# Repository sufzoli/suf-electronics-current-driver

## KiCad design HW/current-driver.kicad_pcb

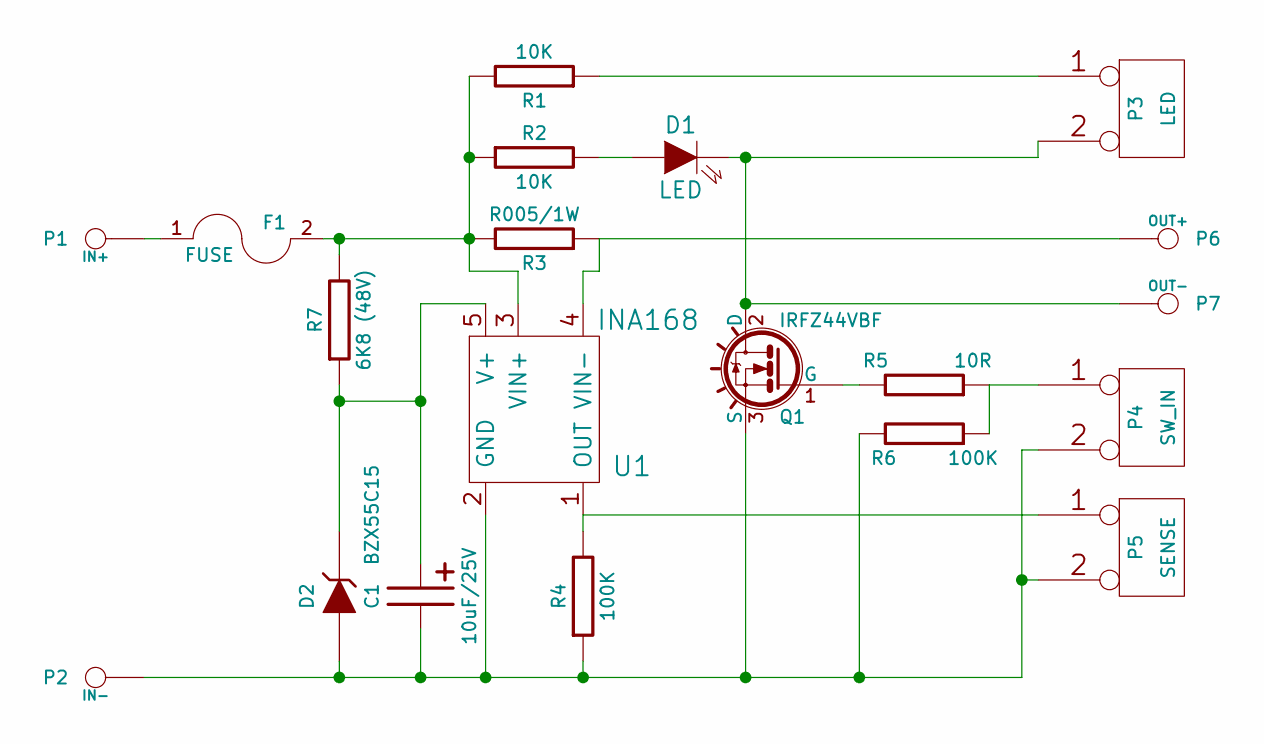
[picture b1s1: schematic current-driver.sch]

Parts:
C1: 10uF/25V; C1P_D2
D1: LED; LED3
D2: BZX55C15; D3
F1: FUSE; AUTOFUSE
P1: IN+; HEADER_6.3
P2: IN-; HEADER_6.3
P3: LED; HDR-2
P4: SW_IN; HDR-2
P5: SENSE; HDR-2
P6: OUT+; HEADER_6.3
P7: OUT-; HEADER_6.3
Q1: IRFZ44VBF; TO220
R1, R2: 10K; R4
R3: R005/1W; R4_5_6
R4, R6: 100K; R4
R5: 10R; R4
R7: 6K8 (48V); R4
U1: INA168; SOT23-5

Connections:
unnamed: Q1.1 (G), R5.1
unnamed: P4.1, R5.2, R6.2
unnamed: P5.1, R4.1, U1.1 (OUT)
unnamed: C1.1, D2.2 (K), R7.2, U1.5 (V+)
unnamed: P3.1, R1.2
unnamed: C1.2, D2.1 (A), P2.1, P4.2 (PM), P5.2 (PM), Q1.3 (S), R4.2, R6.1, U1.2 (GND)
unnamed: D1.2 (K), P3.2 (PM), P7.1, Q1.2 (D)
unnamed: P6.1, R3.2, U1.4 (VIN-)
unnamed: D1.1 (A), R2.1
unnamed: F1.1, P1.1
unnamed: F1.2, R1.1, R2.2, R3.1, R7.1, U1.3 (VIN+)

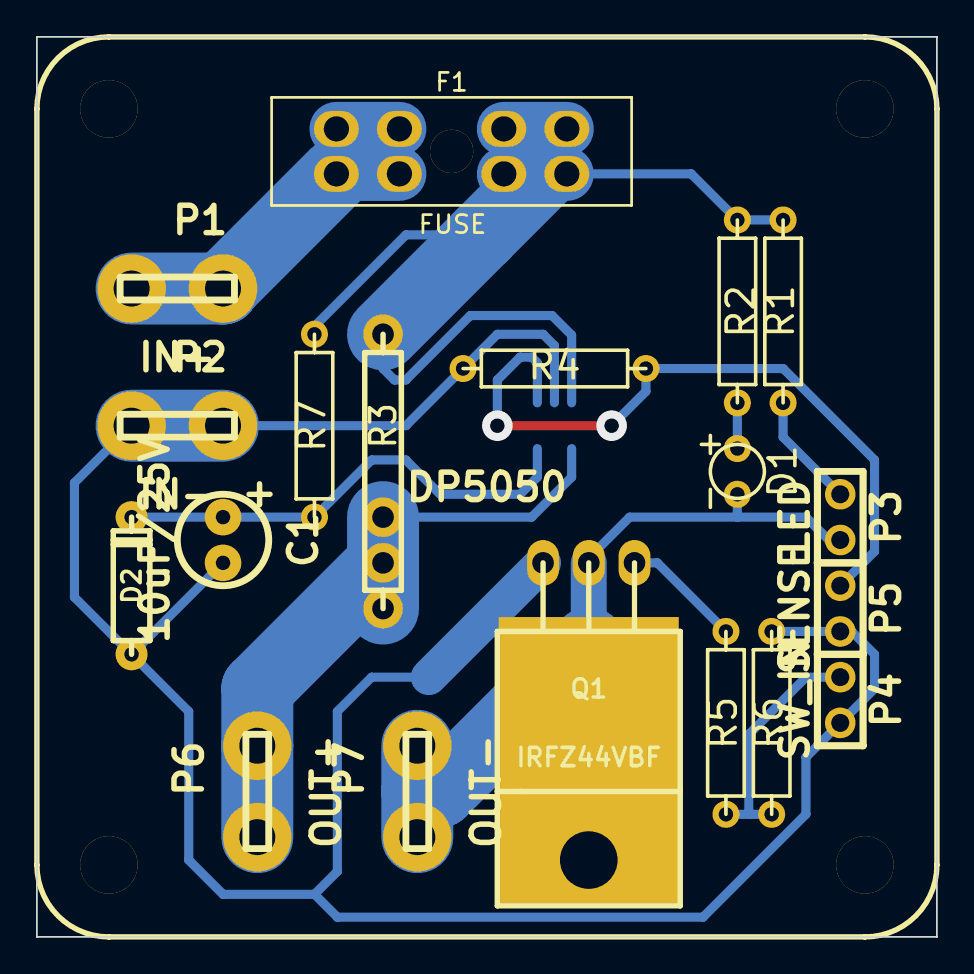
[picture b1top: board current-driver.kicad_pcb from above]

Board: 2 copper layers, 50.0 x 50.0 mm, 21 parts (1 on the bottom side), 11 nets.

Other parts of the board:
DP5050: DP5050

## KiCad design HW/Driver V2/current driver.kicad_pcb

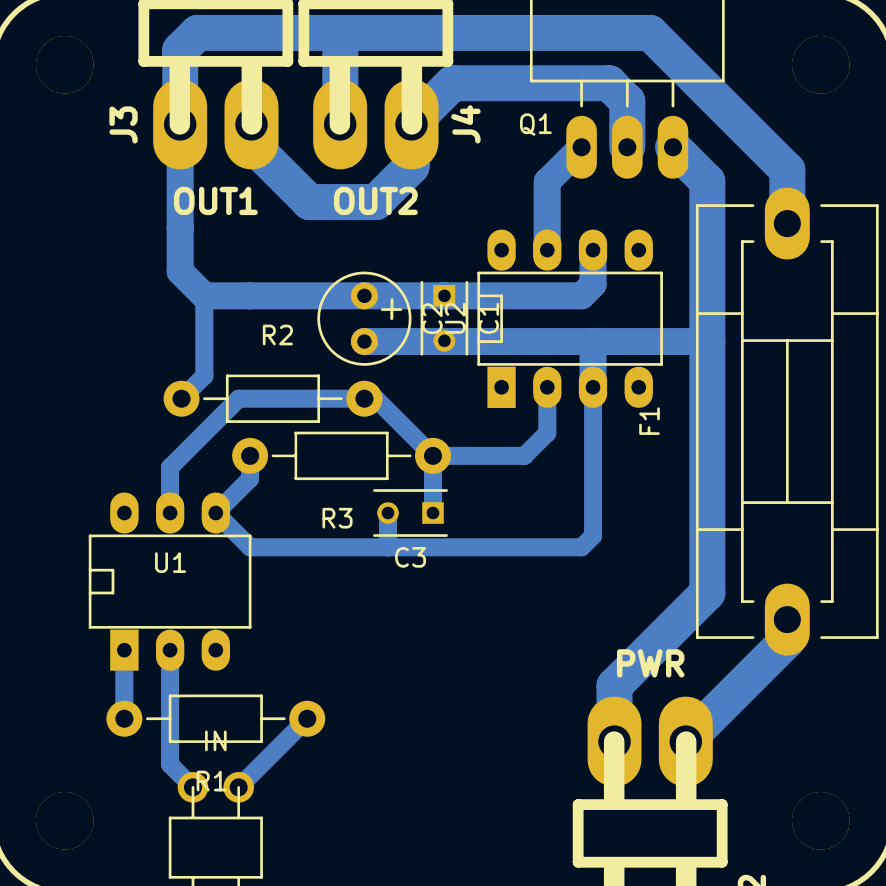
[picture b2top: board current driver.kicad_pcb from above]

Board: 2 copper layers, 15 parts (0 on the bottom side), 9 nets.

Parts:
C1: 100nF; C_Rect_L4_W2.5_P2.5
C2: 4,7uF; Elko_vert_11x5mm_RM2.5
C3: 100pF; C_Rect_L4_W2.5_P2.5
DP5050: DP5050
F1: 10A F; Fuseholder5x20_horiz_SemiClosed_Casing10x25mm
J1: IN; CONN_NCW254-02R
J2: PWR; CONN_NCW396-02R
J3: OUT1; CONN_NCW396-02R
J4: OUT2; CONN_NCW396-02R
Q1: PHP27NQ11T; TO-220_Neutral123_Horizontal_LargePads
R1: 220; Resistor_Horizontal_RM10mm
R2, R3: 1K; Resistor_Horizontal_RM10mm
U1: 4N25; DIP-6__300_ELL
U2: MC33151; DIP-8__300_ELL

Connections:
AGND: J1.2, U1.2
GND: C1.2, C2.2, C3.2, J2.2, Q1.3, R3.2, U1.4, U2.3
unnamed: C3.1, R2.2, R3.1, U1.5, U2.2
unnamed: F1.1, J2.1
unnamed: J1.1, R1.1
unnamed: J3.2, J4.2, Q1.2
unnamed: Q1.1, U2.7
unnamed: R1.2, U1.1
VCC: C1.1, C2.1, F1.2, J3.1, J4.1, R2.1, U2.6

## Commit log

2014-07-23 current-driver.sch v1
2014-07-29 Schematic v2b1
2014-07-30 Schematic v2 finished netlist/pcb added
2014-07-30 PCB v1b1
2014-07-31 PCB v2 almost final
2014-07-31 final 5x5 pcb
2014-08-04 Panelized PCB for printing added
2014-08-06 MOSTFET changed to a logic drive one
2015-09-14 Driver V2 added
